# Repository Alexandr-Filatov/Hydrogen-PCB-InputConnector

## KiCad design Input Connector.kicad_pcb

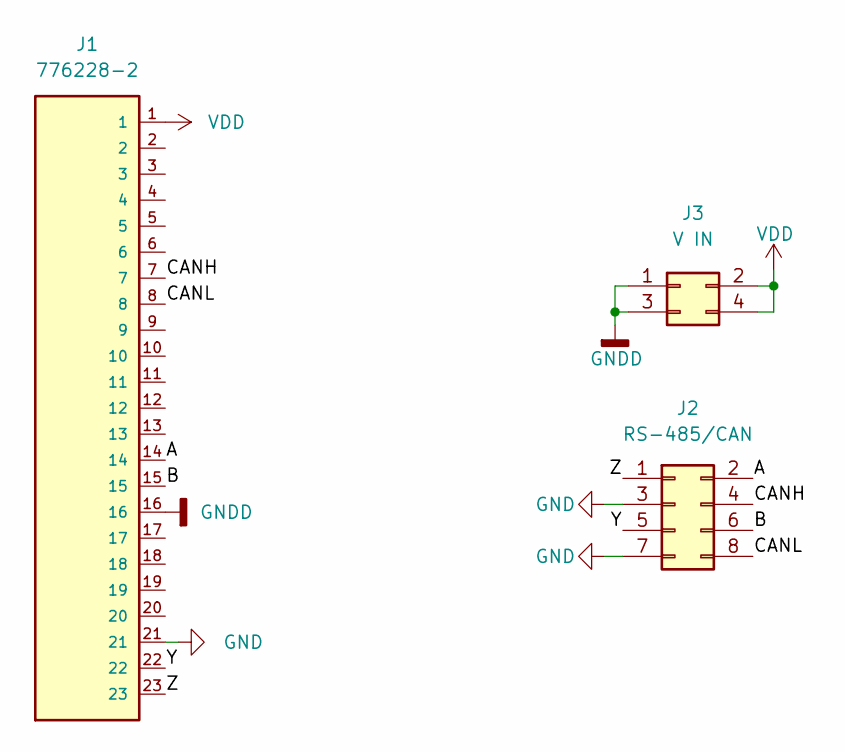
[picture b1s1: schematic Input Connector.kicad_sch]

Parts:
J1: 776228-2; TE_776228-2; PARTREV C13
J2: RS-485/CAN; Molex_Micro-Fit_3.0_43045-0812_2x04_P3.00mm_Vertical
J3: V IN; Molex_Micro-Fit_3.0_43045-0412_2x02_P3.00mm_Vertical

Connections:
/A: J1.14, J2.2
/B: J1.15, J2.6
/CANH: J1.7, J2.4
/CANL: J1.8, J2.8
/Y: J1.22, J2.5
/Z: J1.23, J2.1
GND: J1.21, J2.3, J2.7
GNDD: J1.16, J3.1, J3.3
VDD: J1.1, J3.2, J3.4

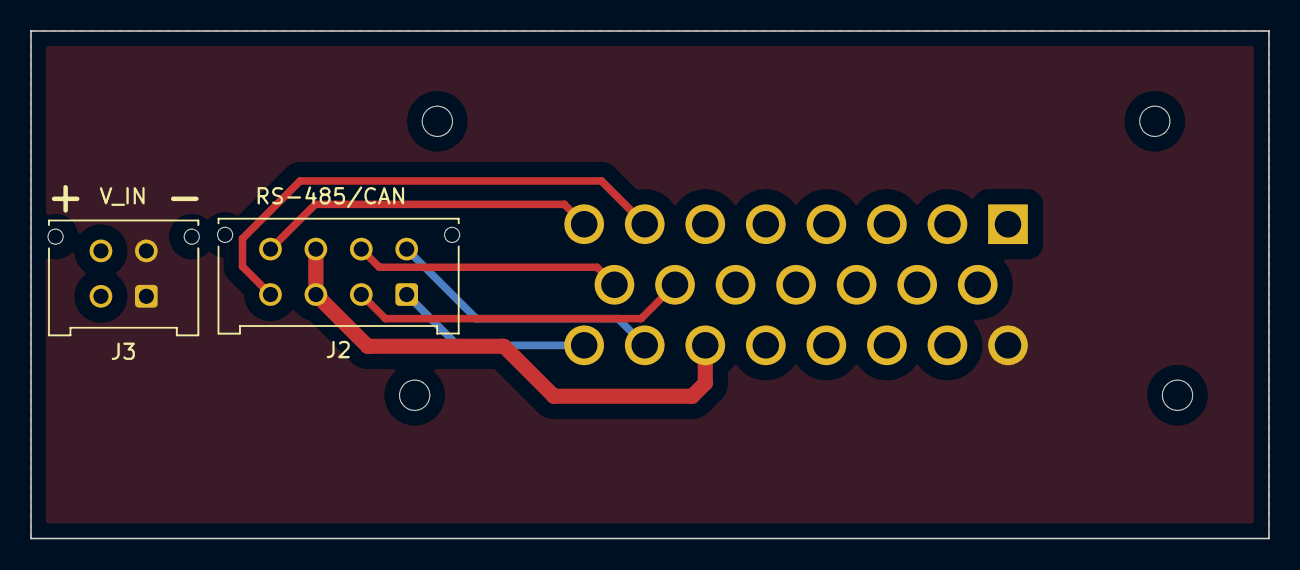
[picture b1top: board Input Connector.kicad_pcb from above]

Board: 2 copper layers, 81.8 x 33.5 mm, 3 parts (1 on the bottom side), 9 nets.

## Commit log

2022-06-02 Первая версия в производство
2022-08-22 Добавил землю RS-484
2022-08-22 Добавил гербера
